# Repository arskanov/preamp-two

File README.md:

# Headphone Amp + Preamp

This project is based on "preamp two" from Max Williams. It has the following features:

  * A precision volume control using a R2R multiplying DAC
  * 3 input selector with mute
  * Dedicated headphone preamp for heavier loads
  * Volume and input control via rotary encoders and an ESP32.
  * Start-up mute.

## Hardware

### MDAC attenuator

Based on a design from a Analog Devices circuit note: http://www.analog.com/en/design-center/reference-designs/hardware-reference-design/circuits-from-the-lab/CN0025.html

This design is also used by a number manufacturers.

  * 65536 linear steps (16bit)
  * Any gain possible, set by OPAMP and resistors
  * Excellent performance
  * Can drive headphones
  * Compact
  * SPI controlled

### Input selector

  * 6x inputs
  * Mute for the output
  * SPI controlled using a MCP23S17
  * Latching relays so no constant current draw (mute is not latching, obviously)
  * Uses high quality Panasonic GQ relays (AGQ)

### RCA board

Designed for [CMC 816 RCA](http://www.audio-cmc.com/rca-jacks/rca-jacks-p_29.html) sockets, they can be soldered directly on to the PCB and are easy to find on eBay or Aliexpress etc.

### Infrared remote control

The IRremote library is from here:
https://github.com/z3t0/Arduino-IRremote

## Bill of materials

### Input selector

| Part name                         | Farnell Part | Detail                                                                                                        | Description        | Notes | Quantity |
|-----------------------------------|--------------|---------------------------------------------------------------------------------------------------------------|--------------------|-------|----------|
| K1-6                              | 1867255      | AGQ2104H                                                                                                      | 1 coil latching    |       | 6        |
| KMUTE                             | 3104813      | AGQ2004H                                                                                                      | Single side stable |       | 1        |
| IC1                               | -            | MCP23S17SO                                                                                                    |                    |       | 1        |
| IC2, IC3                          | -            | ULN2803                                                                                                       |                    |       | 2        |
| R1-12                             | -            |                                                                                                               | 47R, 1206          |       | 12       |
| EXTRA_IO                          | 1675765      | MULTICOMP MC34631 Wire-To-Board Connector, Vertical, MC34 Series, Through Hole, Header, 3, 2.54 mm            |                    |       | 1        |
| X1                                | 1675768      | MULTICOMP MC34635 Wire-To-Board Connector, MC34 Series, Through Hole, Header, 6, 2.54 mm, Tin Plated Contacts |                    |       | 1        |
| POWER                             | 1675764      | MULTICOMP MC34629 Wire-To-Board Connector, Vertical, MC34 Series, Through Hole, Header, 2, 2.54 mm            |                    |       | 1        |
| IN1-6, SEL_OUT, MUTE_IN, MUTE_OUT | 1675765      | MULTICOMP MC34631 Wire-To-Board Connector, Vertical, MC34 Series, Through Hole, Header, 3, 2.54 mm            |                    |       | 9        |
| C2                                | -            | Panasonic E/D SMD (8/6.3mm) or 3.5/8mm leaded                                                                 |                    |       | 1        |
| C1                                | 1414725      | KEMET - C1206C224K5RACTU                                                                                      |                    |       | 1        |
| LED                               | 2217976      | 1206 LED                                                                                                      |                    |       | 1        |
| RLED                              | -            | 1206 Resistor, 1.2K                                                                                           |                    |       | 1        |

### MDAC attenuator

To calculate gain use this formula:

      gain = (R2+R3)/R2
      R1 = (R2*R3)/(R2+R3)

This was copied from the [AD5429/AD5439/AD5449 datasheet](http://www.analog.com/media/en/technical-documentation/data-sheets/AD5429_5439_5449.pdf)

| Part name    | Farnell Part | Detail                     | Description                                      | Notes            | Quantity |
|--------------|--------------|----------------------------|--------------------------------------------------|------------------|----------|
| U2           | 1390687      | TI DAC8812ICPWG4           |                                                  |                  | 1        |
| IC2          | 1438872      | ANALOG DEVICES - AD8599ARZ | Description: IC, OP AMP, DUAL, SMD, SOIC8, 8599  |                  | 1        |
| C1A, C1B     | 1759181      | MULTICOMP - MCCA000310     | Description: CAP, MLCC, C0G/NP0, 2PF, 50V, 0805  |                  | 2        |
| R1A/B        | 1841733      | PANASONIC - ERA8AEB910V    | Description: RESISTOR, 1206, 0.1%, 0.25W, 91R    | 91R (gain of 4)  | 2        |
| R2A/B, R4A/B | 1841735      | PANASONIC - ERA8AEB121V    | Description: RESISTOR, 1206, 0.1%, 0.25W, 120R   | 120R (gain of 4) | 4        |
| R3A/B        | 1841744      | PANASONIC - ERA8AEB361V    | Description: RESISTOR, 1206, 0.1%, 0.25W, 360R   | 360R (gain of 4) | 2        |
| C7           | -            | -                          | Panasonic D/C SMD (6.3/5mm) or 3.5/8mm leaded    |                  | 1        |
| C6, C6       | -            | -                          | Panasonic E/D SMD (8/6.3mm) or 3.5/8mm leaded    |                  | 2        |
| X1           | 1675777      | MULTICOMP MC34649          | Description: HEADER, THT, VERTICAL, 2.54MM, 6WAY |                  | 1        |
| IN, OUT, PWR | 1675765      | MULTICOMP - MC34631        | Description: HEADER, THT, VERTICAL, 2.54MM, 3WAY |                  | 3        |
| C2, C3, C4   | 1414725      | KEMET - C1206C224K5RACTU   | Description: CAP, MLCC, X7R, 220NF, 50V, 1206    |                  | 3        |
| LED          | 2217976      | 1206 LED                   | Description: LED, SMD, 1206 BLUE                 |                  | 1        |
| RLED         | -            | 1206 Resistor, 1.2K        |                                                  |                  | 1        |

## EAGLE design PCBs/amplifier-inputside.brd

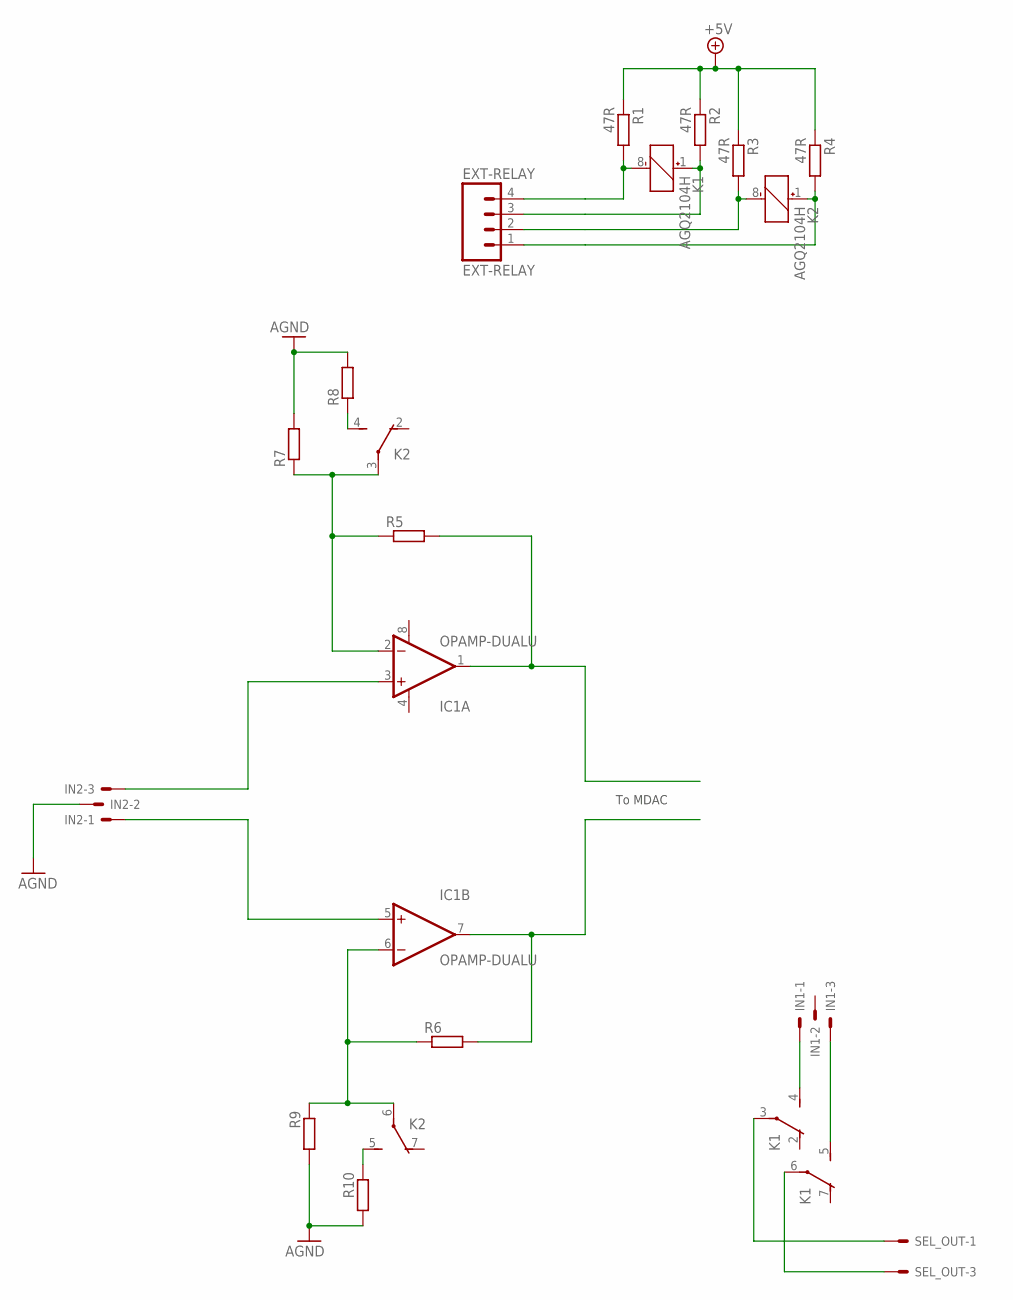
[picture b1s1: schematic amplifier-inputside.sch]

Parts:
EXT-RELAY: EXT-RELAY; MOLEX-1X4
IC1: OPAMP-DUALU; SO08
IN1, IN2: 22-23-2031
K1, K2: AGQ2104H; PCBBOARD
R1, R2, R3, R4: 47R; R1206
R5, R6, R7, R8, R9, R10: R-EU_R1206W; R1206W
SEL_OUT: 22-23-2031

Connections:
+5V: R1.1, R2.1, R3.1, R4.1
AGND: IN2.2, R7.2, R8.2, R9.2, R10.2
INL: K1.3, SEL_OUT.1
INR: K1.6, SEL_OUT.3
unnamed: IN1.1, K1.4 (S)
unnamed: IC1.3 (+IN), IN2.3
unnamed: IN1.3, K1.5 (S)
unnamed: IC1.5 (+IN), IN2.1
unnamed: K1.8 (-), R1.2
unnamed: K2.4 (S), R8.1
unnamed: IC1.1 (OUT), R5.2
unnamed: K1.1 (+), R2.2
unnamed: K2.8 (-), R3.2
unnamed: IC1.7 (OUT), R6.2
unnamed: K2.1 (+), R4.2
unnamed: IC1.2 (-IN), K2.3, R5.1, R7.1
unnamed: K2.5 (S), R10.1
unnamed: IC1.6 (-IN), K2.6, R6.1, R9.1
V+: IC1.8 (V+)
V-: IC1.4 (V-)

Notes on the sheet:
To MDAC

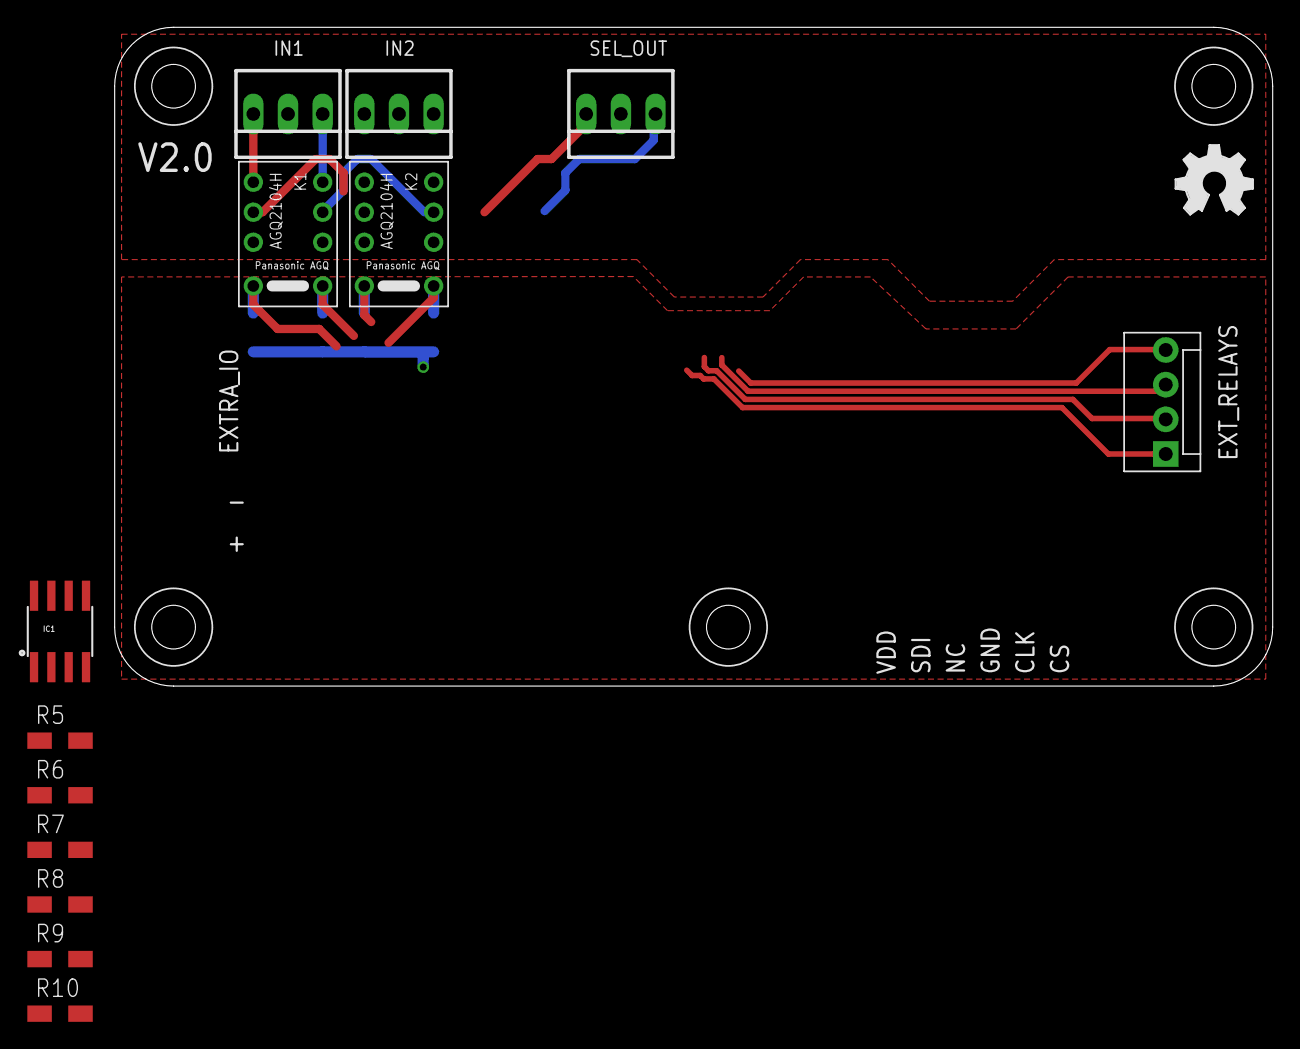
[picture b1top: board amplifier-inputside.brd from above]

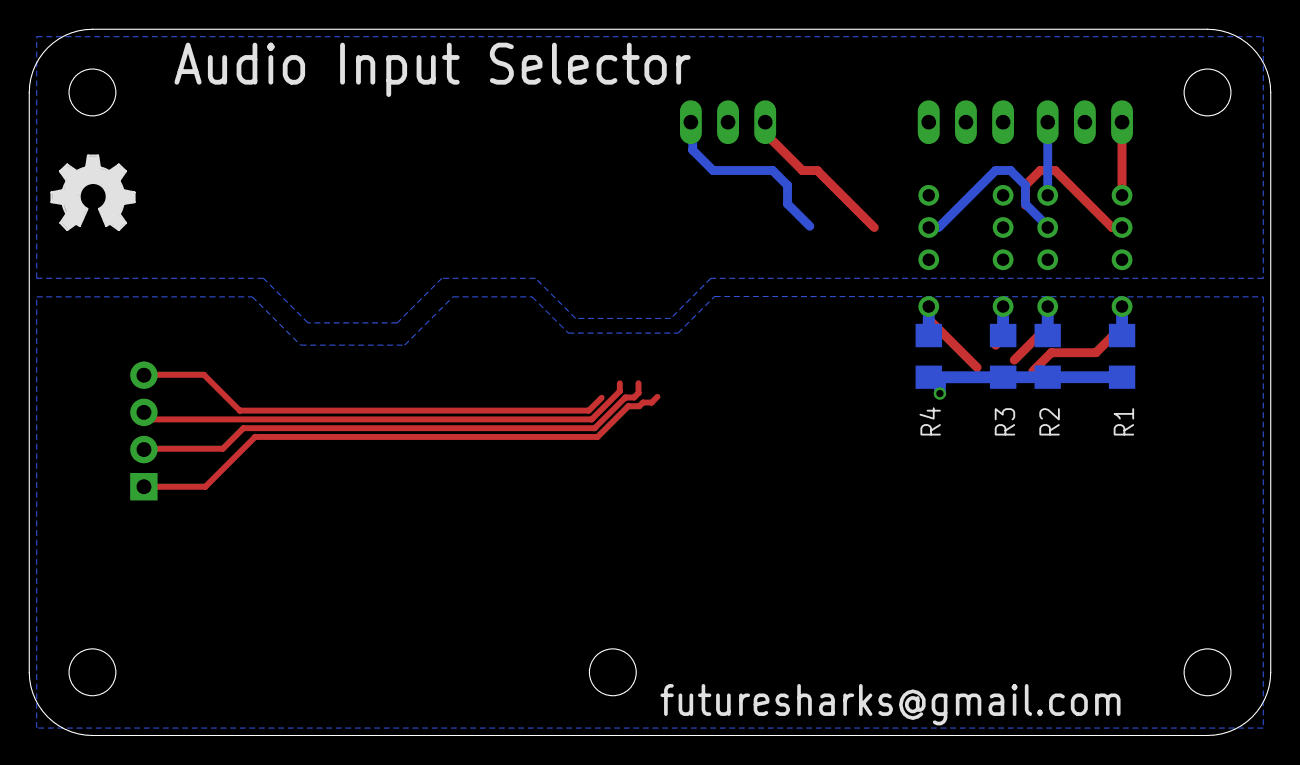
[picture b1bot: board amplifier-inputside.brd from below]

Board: 2 copper layers, 84.8 x 48.3 mm, 24 parts (5 on the bottom side), 18 nets.

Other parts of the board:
LOGO1, LOGO2: OSHW_LOGO_FILLX0200-NT; OSHW_FILLX200_NOTEXT
U$1, U$2, U$3, U$4, U$5: M3_HOLE

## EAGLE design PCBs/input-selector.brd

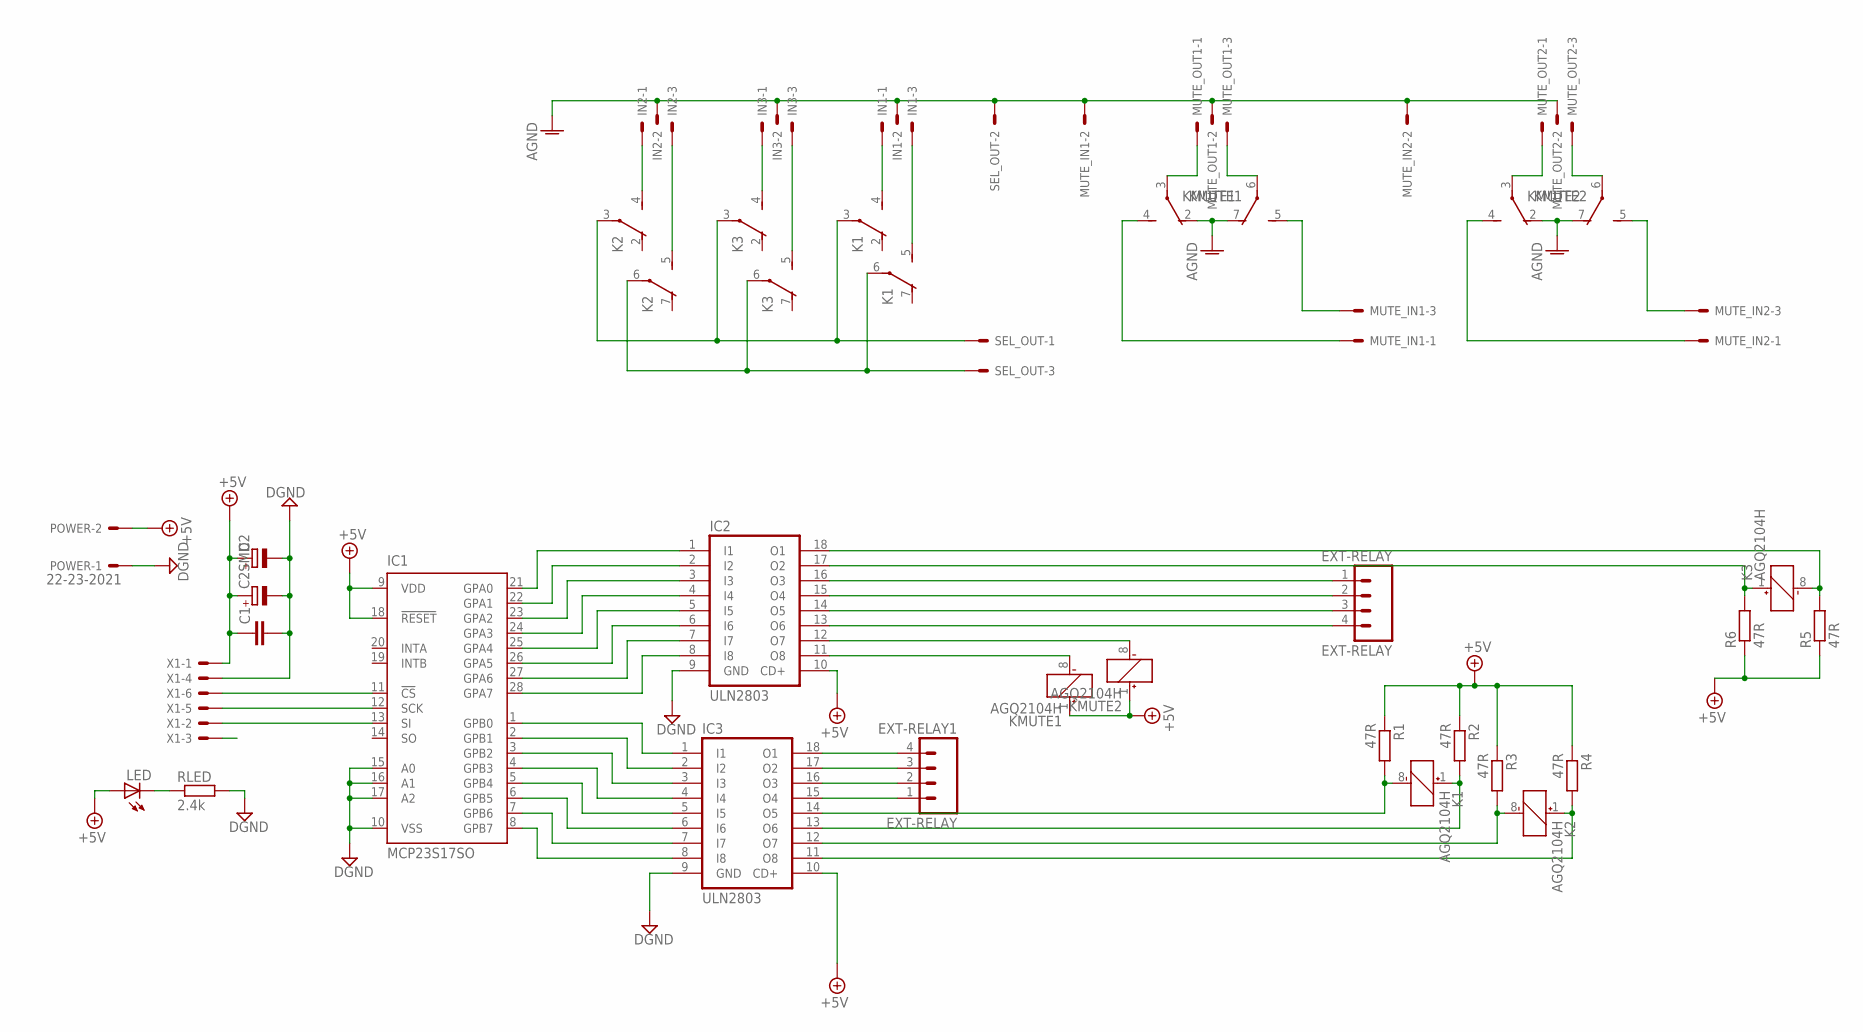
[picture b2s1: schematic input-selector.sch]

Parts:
C1: C-EUC1206; C1206
C2: CPOL-EUE3.5-8; E3,5-8
C2SMD: CPOL-EUE; PANASONIC_E
EXT-RELAY, EXT-RELAY1: EXT-RELAY; MOLEX-1X4
IC1: MCP23S17SO; SO28W
IC2, IC3: ULN2803; SO-18W
IN1, IN2, IN3: 22-23-2031
K1, K2, K3: AGQ2104H; PCBBOARD
KMUTE1, KMUTE2: AGQ2104H; PCBBOARD
LED: LEDSMT1206; 1206
MUTE_IN1, MUTE_IN2: 22-23-2031
MUTE_OUT1, MUTE_OUT2: 22-23-2031
POWER: 22-23-2021
R1, R2, R3, R4, R5, R6: 47R; R1206
RLED: 2.4k; R1206
SEL_OUT: 22-23-2031
X1: 22-23-2061

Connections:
+5V: C1.1, C2.+, C2SMD.+, IC1.9 (VDD), IC1.18 (!RESET), IC2.10 (CD+), IC3.10 (CD+), KMUTE1.1 (+), KMUTE2.1 (+), LED.A, POWER.2, R1.1, R2.1, R3.1, R4.1, R5.1, R6.1, X1.1
AGND: IN1.2, IN2.2, IN3.2, KMUTE1.2 (O), KMUTE1.7 (O), KMUTE2.2 (O), KMUTE2.7 (O), MUTE_IN1.2, MUTE_IN2.2, MUTE_OUT1.2, MUTE_OUT2.2, SEL_OUT.2
CLK: IC1.12 (SCK), X1.5
CS: IC1.11 (!CS), X1.6
DGND: C1.2, C2.-, C2SMD.-, IC1.10 (VSS), IC1.15 (A0), IC1.16 (A1), IC1.17 (A2), IC2.9 (GND), IC3.9 (GND), POWER.1, RLED.2, X1.4
INL: K1.3, K2.3, K3.3, SEL_OUT.1
INR: K1.6, K2.6, K3.6, SEL_OUT.3
unnamed: IN1.1, K1.4 (S)
unnamed: EXT-RELAY1.1, IC3.15 (O4)
unnamed: IN1.3, K1.5 (S)
unnamed: EXT-RELAY1.2, IC3.16 (O3)
unnamed: IC3.14 (O5), K1.8 (-), R1.2
unnamed: IC2.11 (O8), KMUTE1.8 (-)
unnamed: IC1.21 (GPA0), IC2.1 (I1)
unnamed: IC3.13 (O6), K1.1 (+), R2.2
unnamed: IC3.12 (O7), K2.8 (-), R3.2
unnamed: EXT-RELAY1.3, IC3.17 (O2)
unnamed: EXT-RELAY.1, IC2.16 (O3)
unnamed: IC3.11 (O8), K2.1 (+), R4.2
unnamed: EXT-RELAY1.4, IC3.18 (O1)
unnamed: IC2.18 (O1), K3.8 (-), R5.2
unnamed: EXT-RELAY.2, IC2.15 (O4)
unnamed: EXT-RELAY.4, IC2.13 (O6)
unnamed: KMUTE1.6, MUTE_OUT1.3
unnamed: KMUTE1.3, MUTE_OUT1.1
unnamed: IC2.12 (O7), KMUTE2.8 (-)
unnamed: KMUTE2.6, MUTE_OUT2.3
unnamed: IC1.23 (GPA2), IC2.3 (I3)
unnamed: IC2.17 (O2), K3.1 (+), R6.2
unnamed: EXT-RELAY.3, IC2.14 (O5)
unnamed: KMUTE2.3, MUTE_OUT2.1
unnamed: IN2.1, K2.4 (S)
unnamed: IN2.3, K2.5 (S)
unnamed: IN3.1, K3.4 (S)
unnamed: IN3.3, K3.5 (S)
unnamed: IC1.25 (GPA4), IC2.5 (I5)
unnamed: IC1.27 (GPA6), IC2.7 (I7)
unnamed: IC1.1 (GPB0), IC3.1 (I1)
unnamed: IC1.2 (GPB1), IC3.2 (I2)
unnamed: IC1.3 (GPB2), IC3.3 (I3)
unnamed: IC1.4 (GPB3), IC3.4 (I4)
unnamed: IC1.5 (GPB4), IC3.5 (I5)
unnamed: IC1.6 (GPB5), IC3.6 (I6)
unnamed: IC1.7 (GPB6), IC3.7 (I7)
unnamed: IC1.8 (GPB7), IC3.8 (I8)
unnamed: IC1.22 (GPA1), IC2.2 (I2)
unnamed: IC1.24 (GPA3), IC2.4 (I4)
unnamed: IC1.26 (GPA5), IC2.6 (I6)
unnamed: IC1.28 (GPA7), IC2.8 (I8)
unnamed: LED.C, RLED.1
NC: X1.3
OUTL: KMUTE1.4 (S), MUTE_IN1.1
OUTL1: KMUTE2.4 (S), MUTE_IN2.1
OUTR: KMUTE1.5 (S), MUTE_IN1.3
OUTR1: KMUTE2.5 (S), MUTE_IN2.3
SDI: IC1.13 (SI), X1.2

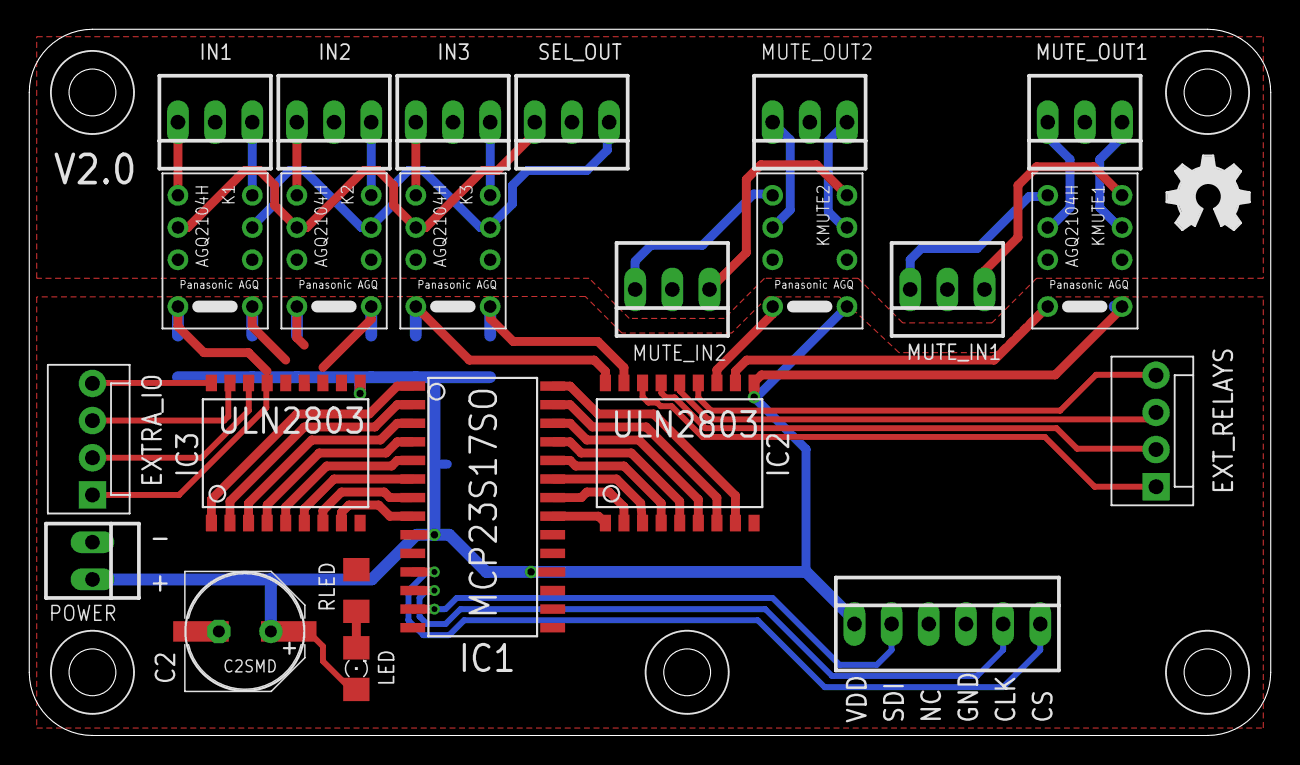
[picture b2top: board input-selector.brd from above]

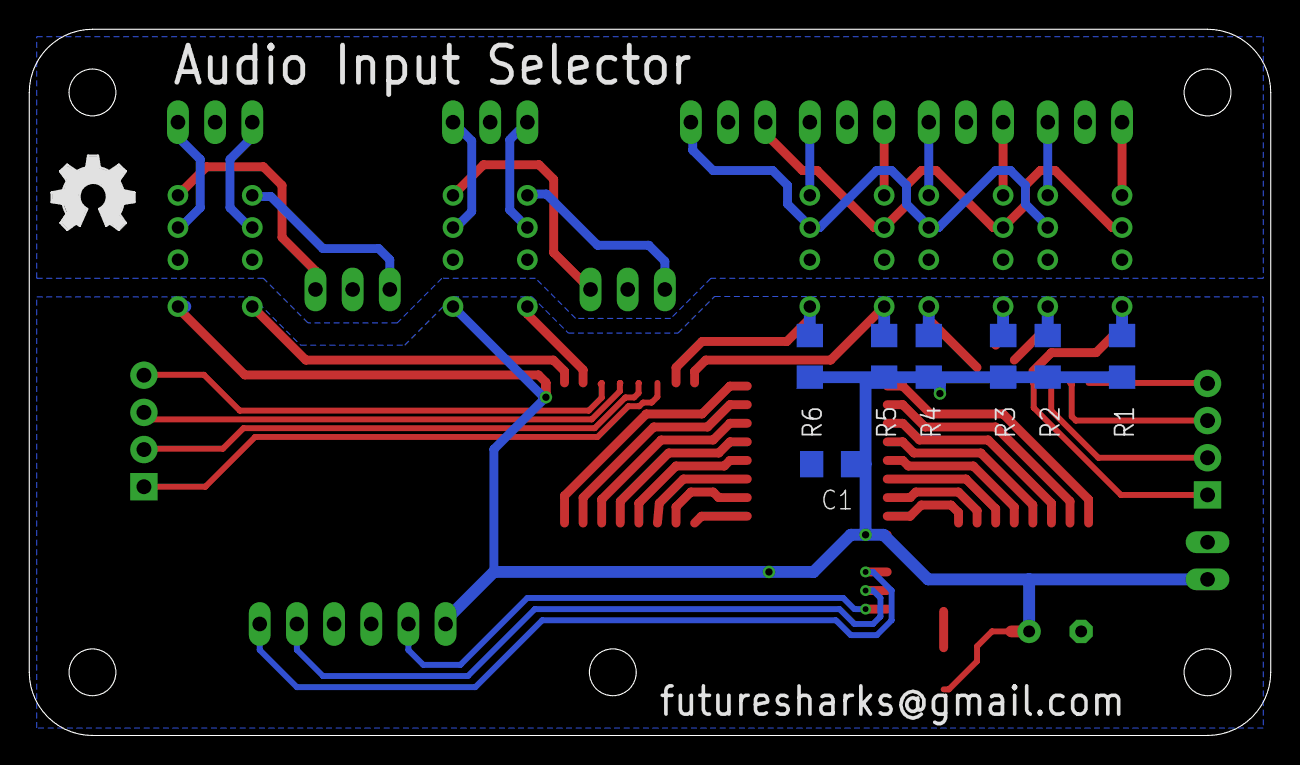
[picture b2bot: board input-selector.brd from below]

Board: 2 copper layers, 84.8 x 48.3 mm, 38 parts (8 on the bottom side), 55 nets.

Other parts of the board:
LOGO1, LOGO2: OSHW_LOGO_FILLX0200-NT; OSHW_FILLX200_NOTEXT
U$1, U$2, U$3, U$4, U$5: M3_HOLE

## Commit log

2016-11-29 Adding gain detail
2018-01-18 Initial commit with first changes
2018-01-18 Finished up connections
2018-01-21 Added amplifier's input side gain switch

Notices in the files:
parts and their libraries:
SparkFun-Connectors: Licensing: Creative Commons ShareAlike 4.0 International - https://creativecommons.org/licenses/by-sa/4.0
